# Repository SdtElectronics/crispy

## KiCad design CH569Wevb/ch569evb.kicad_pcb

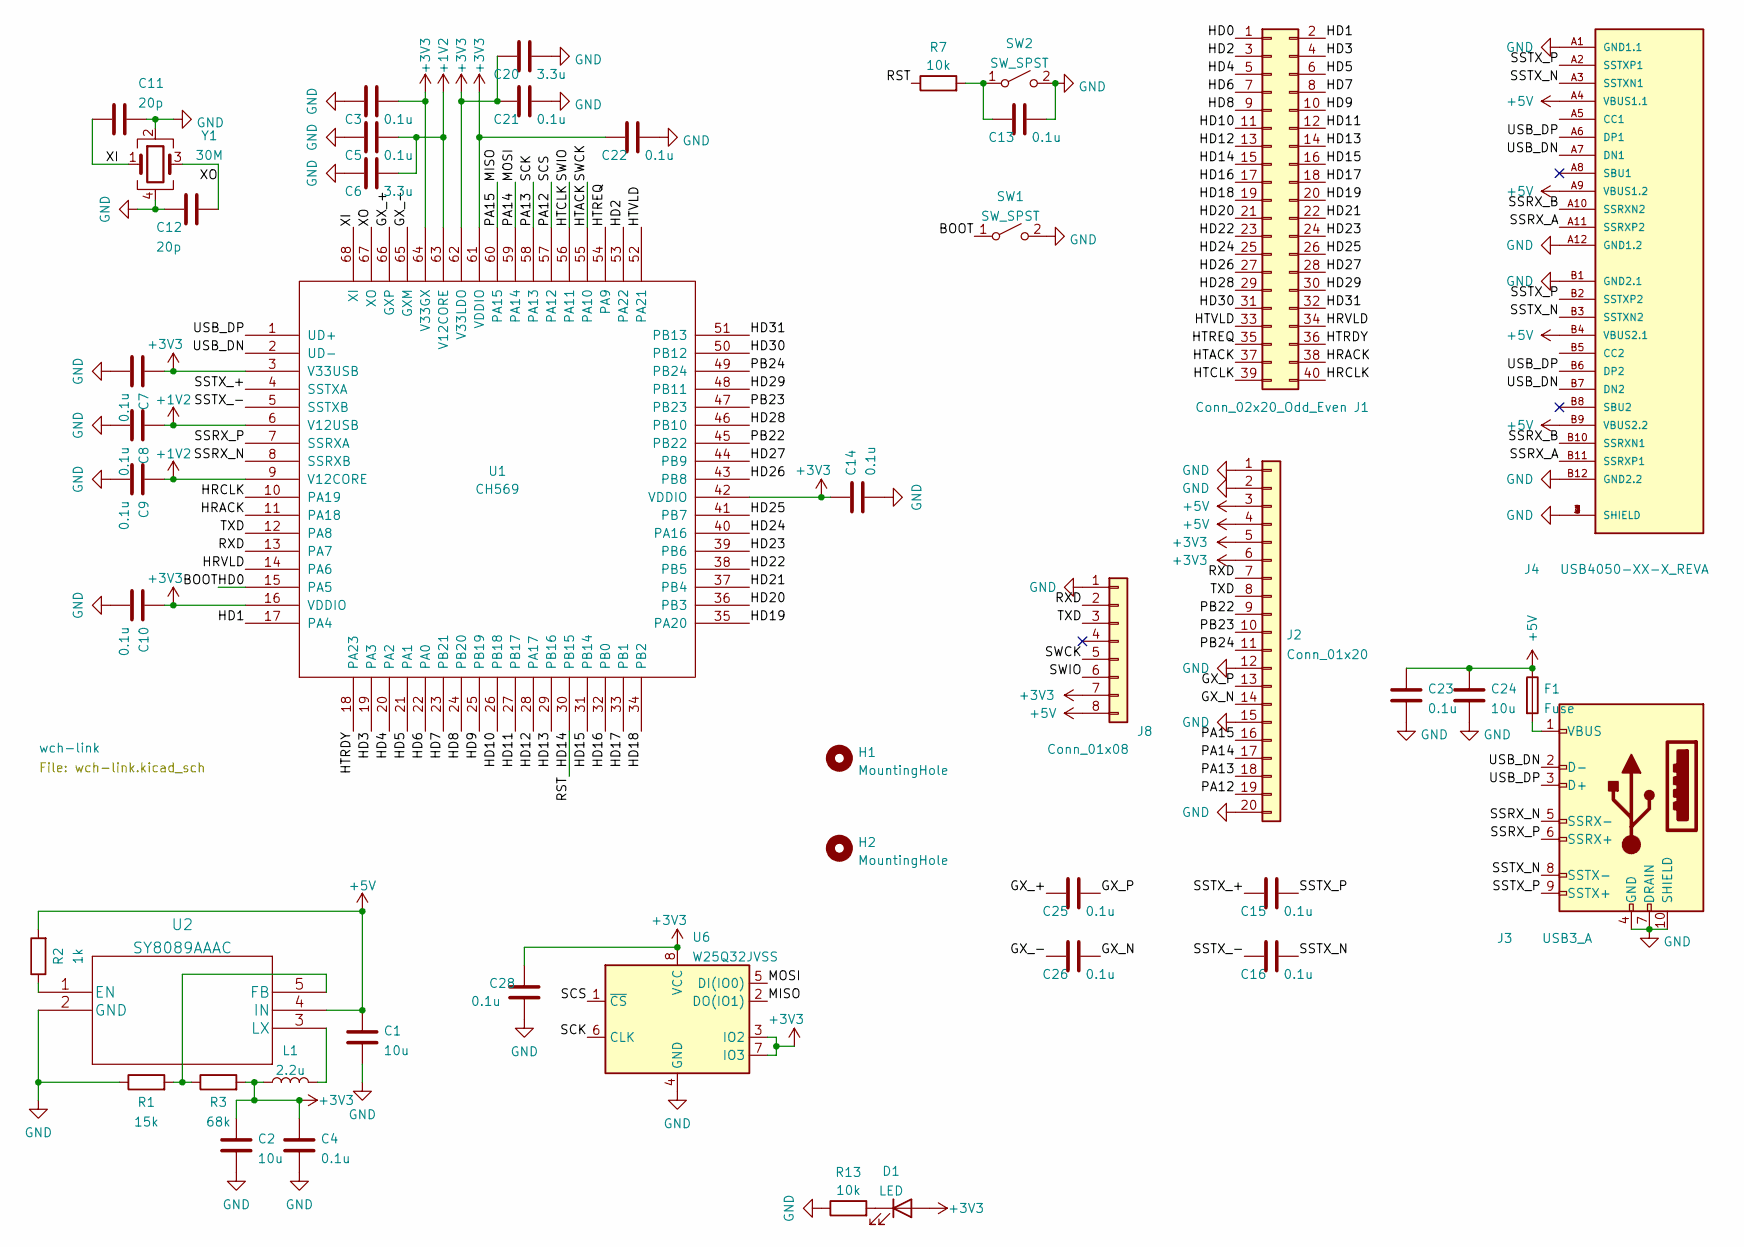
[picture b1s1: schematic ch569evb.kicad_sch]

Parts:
C1, C2, C24: 10u; C_0603_1608Metric
C3, C4, C5, C7, C8, C9, C10, C13, C14, C21, C22, C23, C28: 0.1u; C_0603_1608Metric
C6, C20: 3.3u; C_0603_1608Metric
C11, C12: 20p; C_0603_1608Metric
C15, C16, C25, C26: 0.1u; C_0402_1005Metric
D1: LED; LED_0603_1608Metric
F1: Fuse; Fuse_0805_2012Metric
H1, H2: MountingHole; MountingHole_2.7mm
J1: Conn_02x20_Odd_Even; PinHeader_2x20_P2.54mm_Vertical
J2: Conn_01x20; PinHeader_1x20_P2.54mm_Vertical
J3: USB3_A; GCT_USB1135-15-9-L-B_REVA1
J4: USB4050-XX-X_REVA
J8: Conn_01x08; PinSocket_1x08_P2.54mm_Vertical
L1: 2.2u; L_Wuerth_MAPI-2510
R1: 15k; R_0603_1608Metric
R2: 1k; R_0603_1608Metric
R3: 68k; R_0603_1608Metric
R7, R13: 10k; R_0603_1608Metric
SW1, SW2: SW_SPST; SW_SPST_EVQPE1
U1: CH569; QFN-68-1EP_8x8mm_P0.4mm_EP5.2x5.2mm
U2: SY8089AAAC; SOT-23-5
U6: W25Q32JVSS; SOIC-8_5.23x5.23mm_P1.27mm
Y1: 30M; Crystal_SMD_3225-4Pin_3.2x2.5mm

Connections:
+1V2: C5.1, C6.1, C8.1, C9.1, U1.6 (V12USB), U1.9 (V12CORE), U1.63 (V12CORE)
+3V3: C2.1, C3.1, C4.1, C7.1, C10.1, C14.1, C20.2, C21.2, C22.2, C28.1, D1.2 (A), J2.5, J2.6, J8.7, L1.1, R3.2, U1.3 (V33USB), U1.16 (VDDIO), U1.42 (VDDIO), U1.61 (VDDIO), U1.62 (V33LDO), U1.64 (V33GX), U6.3 (IO2), U6.7 (IO3), U6.8 (VCC); also elsewhere on the board
+5V: C1.1, C23.1, C24.1, F1.1, J2.3, J2.4, J4.A4 (VBUS1.1), J4.A9 (VBUS1.2), J4.B4 (VBUS2.1), J4.B9 (VBUS2.2), J8.8, R2.2, U2.4 (IN); also elsewhere on the board
/BOOT: J1.1, SW1.1 (A), U1.15 (PA5)
/GX_+: C25.2, U1.66 (GXP)
/GX_-: C26.2, U1.65 (GXM)
/GX_N: C26.1, J2.14
/GX_P: C25.1, J2.13
/HD1: J1.2, U1.17 (PA4)
/HD2: J1.3, U1.53 (PA22)
/HD3: J1.4, U1.19 (PA3)
/HD4: J1.5, U1.20 (PA2)
/HD5: J1.6, U1.21 (PA1)
/HD6: J1.7, U1.22 (PA0)
/HD7: J1.8, U1.23 (PB21)
/HD8: J1.9, U1.24 (PB20)
/HD9: J1.10, U1.25 (PB19)
/HD10: J1.11, U1.26 (PB18)
/HD11: J1.12, U1.27 (PB17)
/HD12: J1.13, U1.28 (PA17)
/HD13: J1.14, U1.29 (PB16)
/HD14: J1.15, R7.1, U1.30 (PB15)
/HD15: J1.16, U1.31 (PB14)
/HD16: J1.17, U1.32 (PB0)
/HD17: J1.18, U1.33 (PB1)
/HD18: J1.19, U1.34 (PB2)
/HD19: J1.20, U1.35 (PA20)
/HD20: J1.21, U1.36 (PB3)
/HD21: J1.22, U1.37 (PB4)
/HD22: J1.23, U1.38 (PB5)
/HD23: J1.24, U1.39 (PB6)
/HD24: J1.25, U1.40 (PA16)
/HD25: J1.26, U1.41 (PB7)
/HD26: J1.27, U1.43 (PB8)
/HD27: J1.28, U1.44 (PB9)
/HD28: J1.29, U1.46 (PB10)
/HD29: J1.30, U1.48 (PB11)
/HD30: J1.31, U1.50 (PB12)
/HD31: J1.32, U1.51 (PB13)
/HRACK: J1.38, U1.11 (PA18)
/HRCLK: J1.40, U1.10 (PA19)
/HRVLD: J1.34, U1.14 (PA6)
/HTACK: J1.37, J8.5, U1.55 (PA10)
/HTCLK: J1.39, J8.6, U1.56 (PA11)
/HTRDY: J1.36, U1.18 (PA23)
/HTREQ: J1.35, U1.54 (PA9)
/HTVLD: J1.33, U1.52 (PA21)
/MISO: J2.16, U1.60 (PA15), U6.2 (DO(IO1))
/MOSI: J2.17, U1.59 (PA14), U6.5 (DI(IO0))
/PA12: J2.19, U1.57 (PA12), U6.1 (~CS)
/PA13: J2.18, U1.58 (PA13), U6.6 (CLK)
/PB22: J2.9, U1.45 (PB22)
/PB23: J2.10, U1.47 (PB23)
/PB24: J2.11, U1.49 (PB24)
/RXD: J2.7, J8.2, U1.13 (PA7)
/SSRX_N: J3.5 (SSRX-), U1.8 (SSRXB)
/SSRX_P: J3.6 (SSRX+), U1.7 (SSRXA)
/SSTX_+: C15.2, U1.4 (SSTXA)
/SSTX_-: C16.2, U1.5 (SSTXB)
/SSTX_N: C16.1, J3.8 (SSTX-), J4.A3 (SSTXN1), J4.B3 (SSTXN2)
/SSTX_P: C15.1, J3.9 (SSTX+), J4.A2 (SSTXP1), J4.B2 (SSTXP2)
/TXD: J2.8, J8.3, U1.12 (PA8)
/USB_DN: J3.2 (D-), J4.A7 (DN1), J4.B7 (DN2), U1.2 (UD-)
/USB_DP: J3.3 (D+), J4.A6 (DP1), J4.B6 (DP2), U1.1 (UD+)
/XI: C11.2, U1.68 (XI), Y1.1
/XO: C12.1, U1.67 (XO), Y1.3
GND: C1.2, C2.2, C3.2, C4.2, C5.2, C6.2, C7.2, C8.2, C9.2, C10.2, C11.1, C12.2, C13.1, C14.2, C20.1, C21.1, C22.1, C23.2, C24.2, C28.2, J2.1, J2.2, J2.12, J2.15, J2.20, J3.4 (GND), J3.7 (DRAIN), J3.10 (SHIELD), J3.S1, J3.S2, J4.1 (SHIELD), J4.2 (SHIELD), J4.3 (SHIELD), J4.4 (SHIELD), J4.A1 (GND1.1), J4.A12 (GND1.2), J4.B1 (GND2.1), J4.B12 (GND2.2), J8.1, R1.1, R13.1, SW1.2 (B), SW2.2 (B), U1.69, U2.2 (GND), U6.4 (GND), Y1.2, Y1.4; also elsewhere on the board
unnamed: C13.2, R7.2, SW2.1 (A)
unnamed: D1.1 (K), R13.2
unnamed: F1.2, J3.1 (VBUS)
unnamed: J4.A10 (SSRXN2), J4.B10 (SSRXN1)
unnamed: J4.A11 (SSRXP2), J4.B11 (SSRXP1)
unnamed: L1.2, U2.3 (LX)
unnamed: R1.2, R3.1, U2.5 (FB)
unnamed: R2.1, U2.1 (EN)

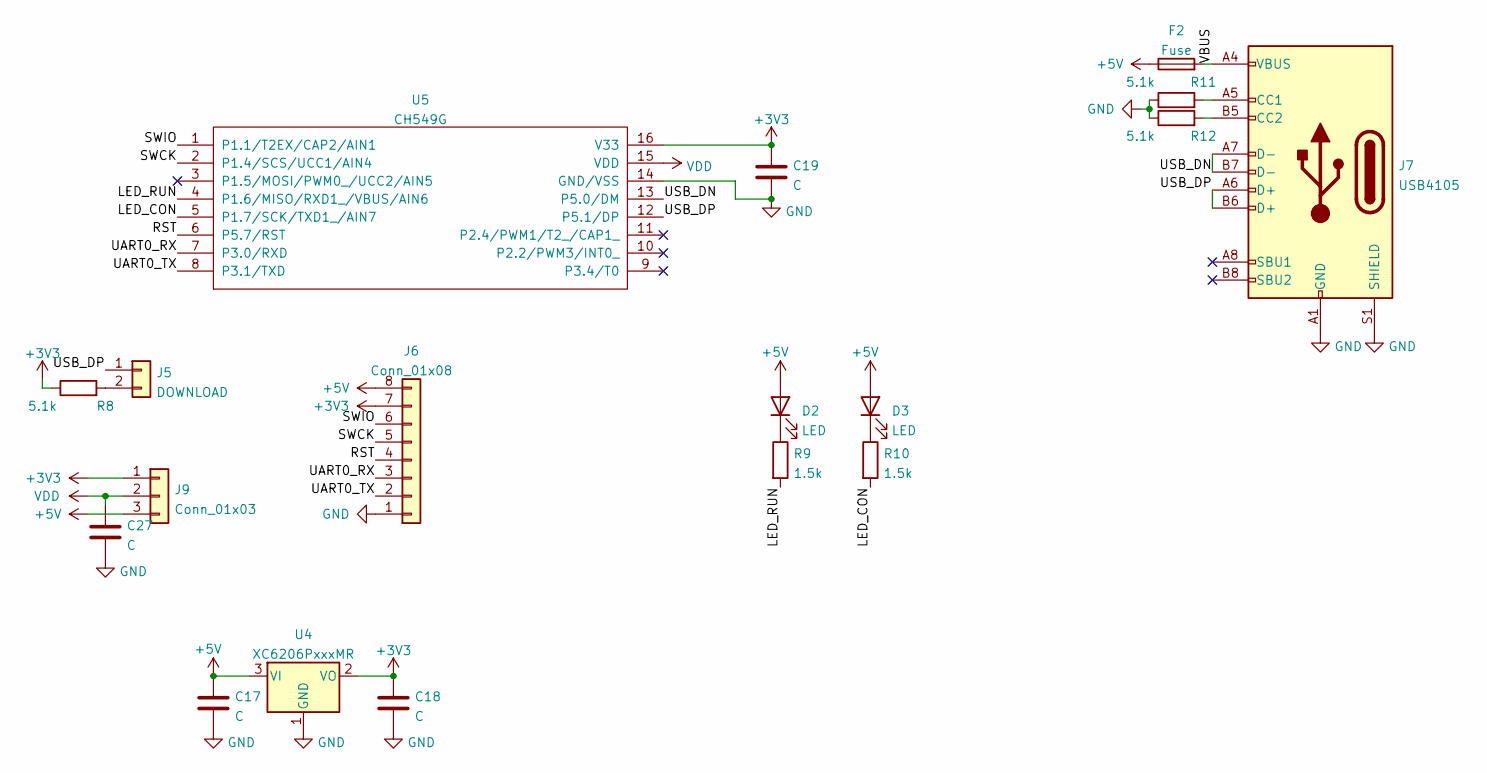
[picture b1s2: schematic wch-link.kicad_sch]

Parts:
C17, C18, C19, C27: C; C_0603_1608Metric
D2, D3: LED; LED_0603_1608Metric
F2: Fuse; Fuse_0805_2012Metric
J5: DOWNLOAD; PinHeader_1x02_P2.54mm_Vertical
J6: Conn_01x08; PinHeader_1x08_P2.54mm_Vertical
J7: USB4105; USB_C_Receptacle_Palconn_UTC16-G
J9: Conn_01x03; PinSocket_1x03_P2.54mm_Vertical
R8, R11, R12: 5.1k; R_0603_1608Metric
R9, R10: 1.5k; R_0603_1608Metric
U4: XC6206PxxxMR; SOT-23
U5: CH549G; SOP-16_3.9x9.9mm_P1.27mm

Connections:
+3V3: C18.1, C19.1, J6.7, J9.1, R8.1, U4.2 (VO), U5.16 (V33); also elsewhere on the board
+5V: C17.1, D2.2 (A), D3.2 (A), F2.1, J6.8, J9.3, U4.3 (VI); also elsewhere on the board
/wch-link/LED_CON: R10.2, U5.5 (P1.7/SCK/TXD1_/AIN7)
/wch-link/LED_RUN: R9.2, U5.4 (P1.6/MISO/RXD1_/VBUS/AIN6)
/wch-link/RST: J6.4, U5.6 (P5.7/RST)
/wch-link/SWCK: J6.5, U5.2 (P1.4/SCS/UCC1/AIN4)
/wch-link/SWIO: J6.6, U5.1 (P1.1/T2EX/CAP2/AIN1)
/wch-link/UART0_RX: J6.3, U5.7 (P3.0/RXD)
/wch-link/UART0_TX: J6.2, U5.8 (P3.1/TXD)
/wch-link/USB_DN: J7.A7 (D-), J7.B7 (D-), U5.13 (P5.0/DM)
/wch-link/USB_DP: J5.1, J7.A6 (D+), J7.B6 (D+), U5.12 (P5.1/DP)
/wch-link/VBUS: F2.2, J7.A4 (VBUS), J7.A9 (VBUS), J7.B4 (VBUS), J7.B9 (VBUS)
GND: C17.2, C18.2, C19.2, C27.2, J6.1, J7.A1 (GND), J7.A12 (GND), J7.B1 (GND), J7.B12 (GND), J7.S1 (SHIELD), R11.1, R12.1, U4.1 (GND), U5.14 (GND/VSS); also elsewhere on the board
unnamed: D2.1 (K), R9.1
unnamed: D3.1 (K), R10.1
unnamed: J5.2, R8.2
unnamed: J7.A5 (CC1), R11.2
unnamed: J7.B5 (CC2), R12.2
VDD: C27.1, J9.2, U5.15 (VDD)

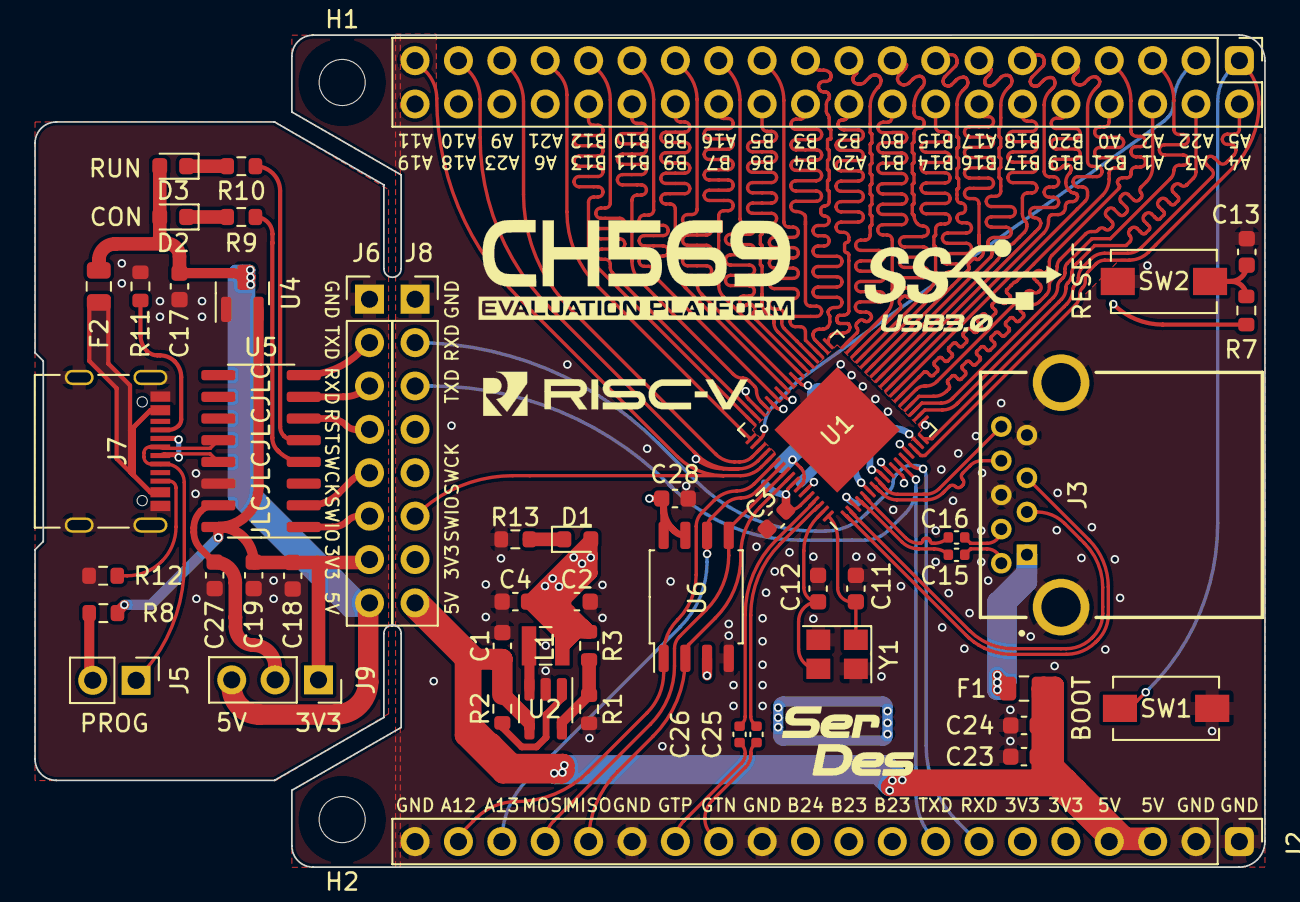
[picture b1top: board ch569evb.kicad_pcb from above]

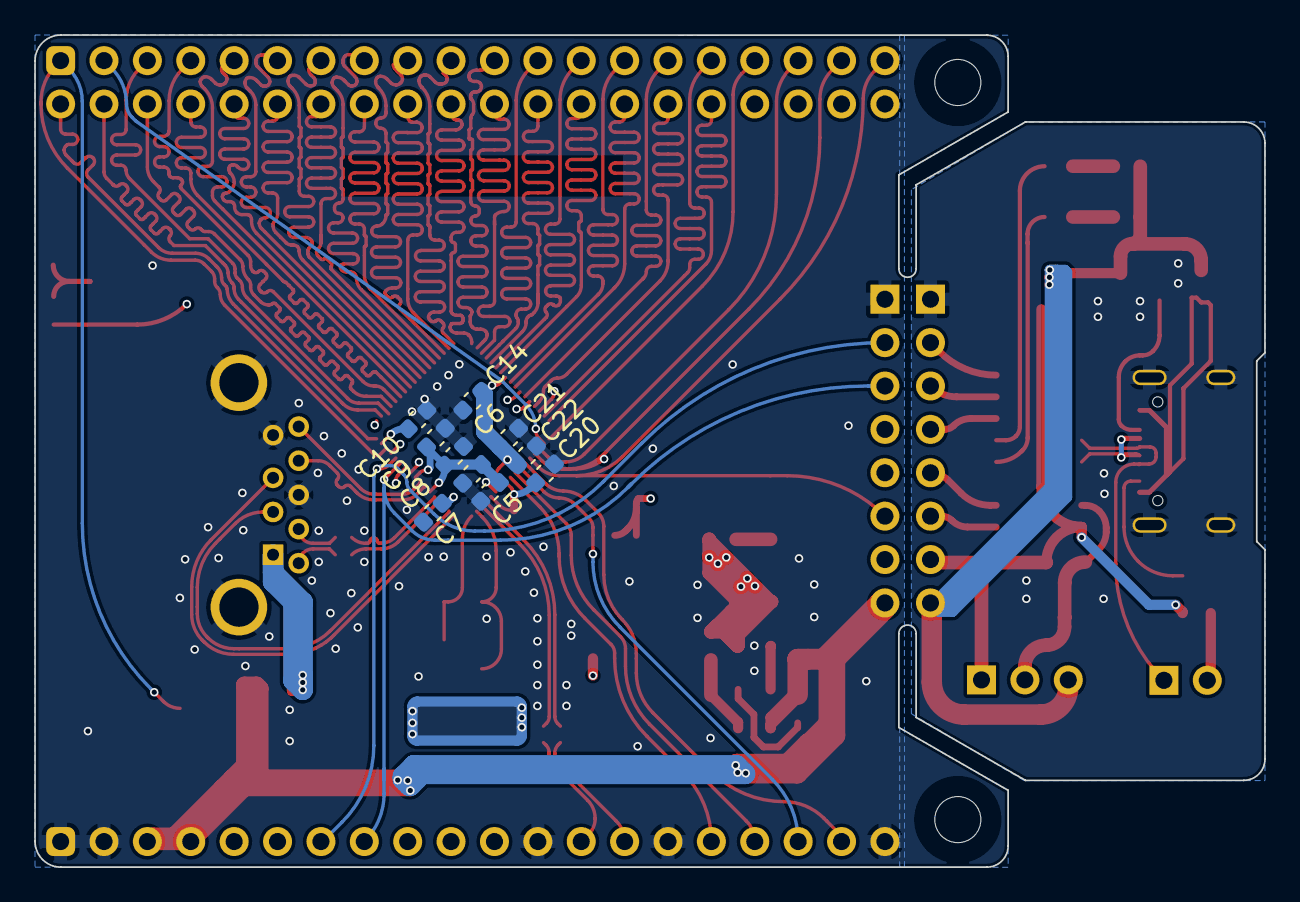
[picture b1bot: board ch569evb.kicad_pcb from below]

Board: 4 copper layers, 72.0 x 48.7 mm, 63 parts (10 on the bottom side), 89 nets.

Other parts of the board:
Ref**: Val**; 5690

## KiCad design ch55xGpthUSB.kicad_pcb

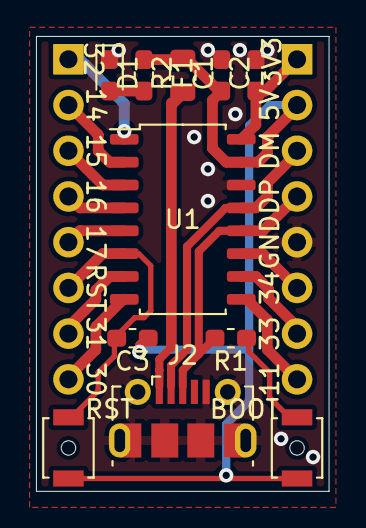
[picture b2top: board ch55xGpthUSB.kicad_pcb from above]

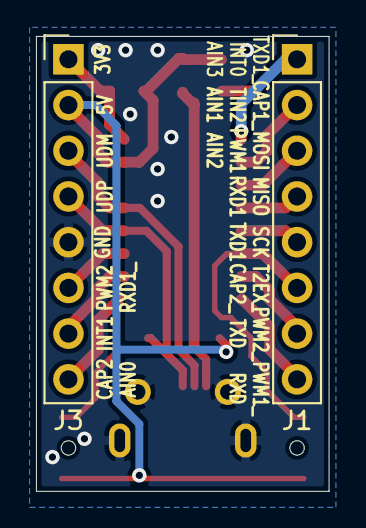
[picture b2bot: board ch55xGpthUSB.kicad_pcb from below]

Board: 2 copper layers, 16.3 x 25.3 mm, 13 parts (2 on the bottom side), 19 nets.

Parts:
BOOT: SW_SPST; SW_SPST_B3U-1000P-B
C1, C2, C3: C; C_0603_1608Metric_Pad1.05x0.95mm_HandSolder
D1: LED; LED_0603_1608Metric_Pad1.05x0.95mm_HandSolder
F1: Fuse; Fuse_0805_2012Metric
J1, J3: Conn_01x08; PinHeader_1x08_P2.54mm_Vertical
J2: USB_B_Micro; USB_Micro-B_Molex-105017-0001
R1, R2: R; R_0603_1608Metric_Pad1.05x0.95mm_HandSolder
RST: SW_SPST; SW_SPST_B3U-1000P-B
U1: CH55x; SOP-16_4.55x10.3mm_P1.27mm

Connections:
+3V3: C2.1, J3.1, U1.16
+5V: BOOT.2, C1.1, C3.1, F1.1, J3.2, R2.2, RST.2, U1.15
/DM: J2.2, J3.3, U1.13
/DP: J2.3, J3.4, R1.2, U1.12
/P1.1: J3.8, U1.9
/P3.3: J3.7, U1.10
/P3.4: J3.6, U1.11
/RST: C3.2, J1.6, RST.1, U1.6
GND: C1.2, C2.2, D1.1, J2.5, J2.6, J3.5, U1.14
unnamed: D1.2, R2.1
unnamed: F1.2, J2.1
unnamed: J1.1, U1.1
unnamed: J1.2, U1.2
unnamed: J1.3, U1.3
unnamed: J1.4, U1.4
unnamed: J1.5, U1.5
unnamed: J1.7, U1.7
unnamed: J1.8, U1.8
unnamed: BOOT.1, R1.1

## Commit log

2021-03-17 add README
2022-04-20 repurpose the repository
2022-04-26 add CH569Wevb
